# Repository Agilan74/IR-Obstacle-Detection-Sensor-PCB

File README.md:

# IR Obstacle Detection Sensor PCB

A custom-designed IR obstacle detection sensor PCB developed using KiCad and LM358 operational amplifier for robotics, automation, and STEM applications.

# IR Obstacle Detection Sensor PCB

## Overview

This project is a custom IR Obstacle Detection Sensor PCB designed using KiCad.

## Features

- LM358 based design
- IR LED transmitter
- Photodiode receiver
- 100nF and 10uF filtering capacitors
- Compact PCB layout

## Applications

- Obstacle Detection Robots
- Line Following Robots
- Automation Systems
- STEM Learning Projects

## Circuit Operation

The IR LED continuously emits infrared light.

When an object comes close to the sensor, the emitted infrared light reflects back and is detected by the photodiode.

The LM358 operational amplifier processes this signal and produces an output indicating the presence of an object.

## Schematic

## PCB Layout

## 3D View

## Software Used

- KiCad 9

## Manufacturing Files

Gerber and drill files required for PCB fabrication are available in the Gerber_Files directory.

## Author

Agilan Loganathan

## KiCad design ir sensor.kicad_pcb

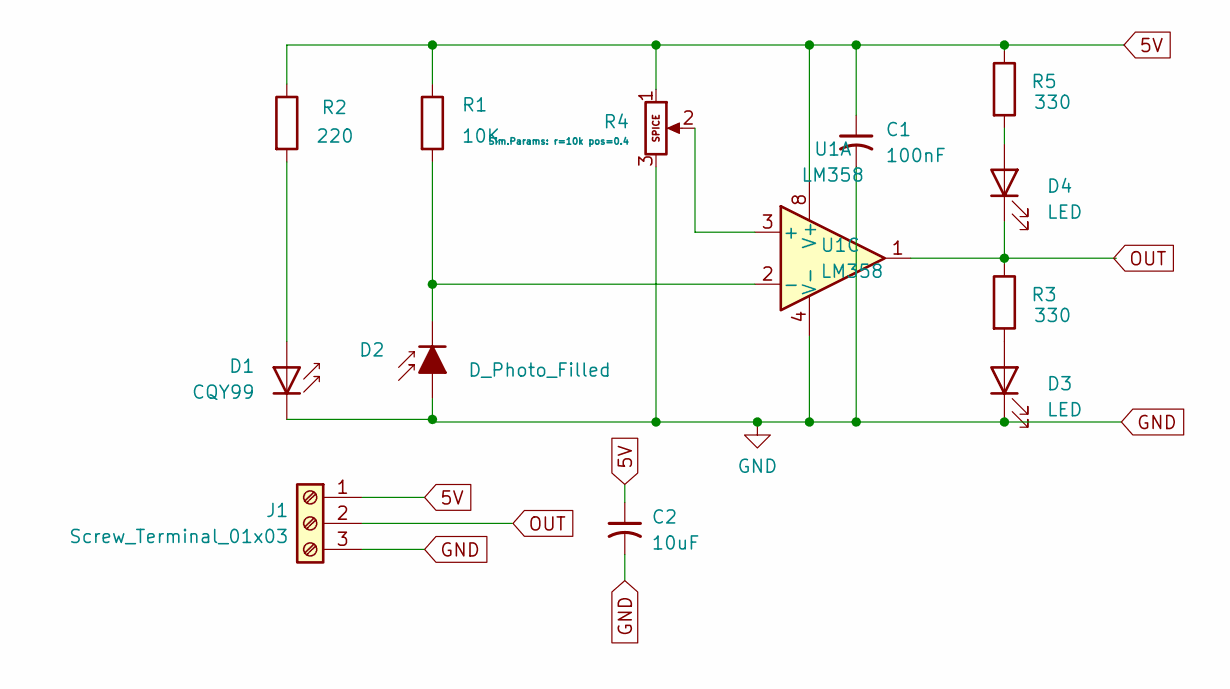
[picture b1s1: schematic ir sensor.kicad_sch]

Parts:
C1: 100nF; C_0805_2012Metric
C2: 10uF; C_0805_2012Metric
D1: CQY99; LED_D5.0mm_Horizontal_O1.27mm_Z3.0mm_Clear
D2: D_Photo_Filled; LED_D5.0mm_IRBlack
D3, D4: LED; LED_Cree-XHP50_3V_HighDensity
J1: Screw_Terminal_01x03; TerminalBlock_MaiXu_MX126-5.0-03P_1x03_P5.00mm
R1: 10K; R_Axial_DIN0204_L3.6mm_D1.6mm_P7.62mm_Horizontal
R2: 220; R_Axial_DIN0204_L3.6mm_D1.6mm_P7.62mm_Horizontal
R3, R5: 330; R_Axial_DIN0204_L3.6mm_D1.6mm_P7.62mm_Horizontal
R4: Potentiometer; Potentiometer_Bourns_3214J_Horizontal
U1: LM358; CERDIP-8_W7.62mm_SideBrazed

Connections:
5V: C1.1, C2.1, J1.1, R1.1, R2.1, R4.1, R5.1, U1.8 (V+)
GND: C1.2, C2.2, D1.1 (K), D2.2 (A), D3.1 (K), J1.3, R4.3, U1.4 (V-)
unnamed: D1.2 (A), R2.2
unnamed: D2.1 (K), R1.2, U1.2 (-)
unnamed: D3.2 (A), R3.2
unnamed: D4.2 (A), R5.2
unnamed: R4.2, U1.3 (+)
OUT: D4.1 (K), J1.2, R3.1, U1.1

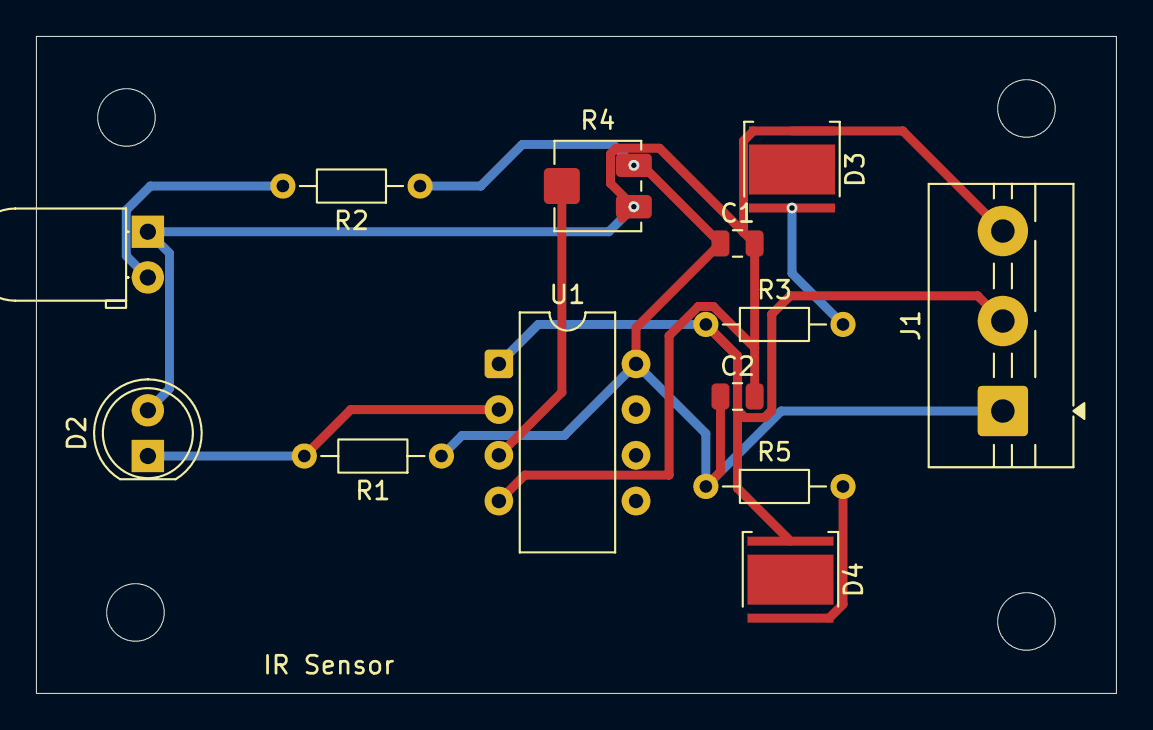
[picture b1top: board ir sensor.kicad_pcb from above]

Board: 2 copper layers, 60.0 x 36.5 mm, 13 parts (0 on the bottom side), 8 nets.
